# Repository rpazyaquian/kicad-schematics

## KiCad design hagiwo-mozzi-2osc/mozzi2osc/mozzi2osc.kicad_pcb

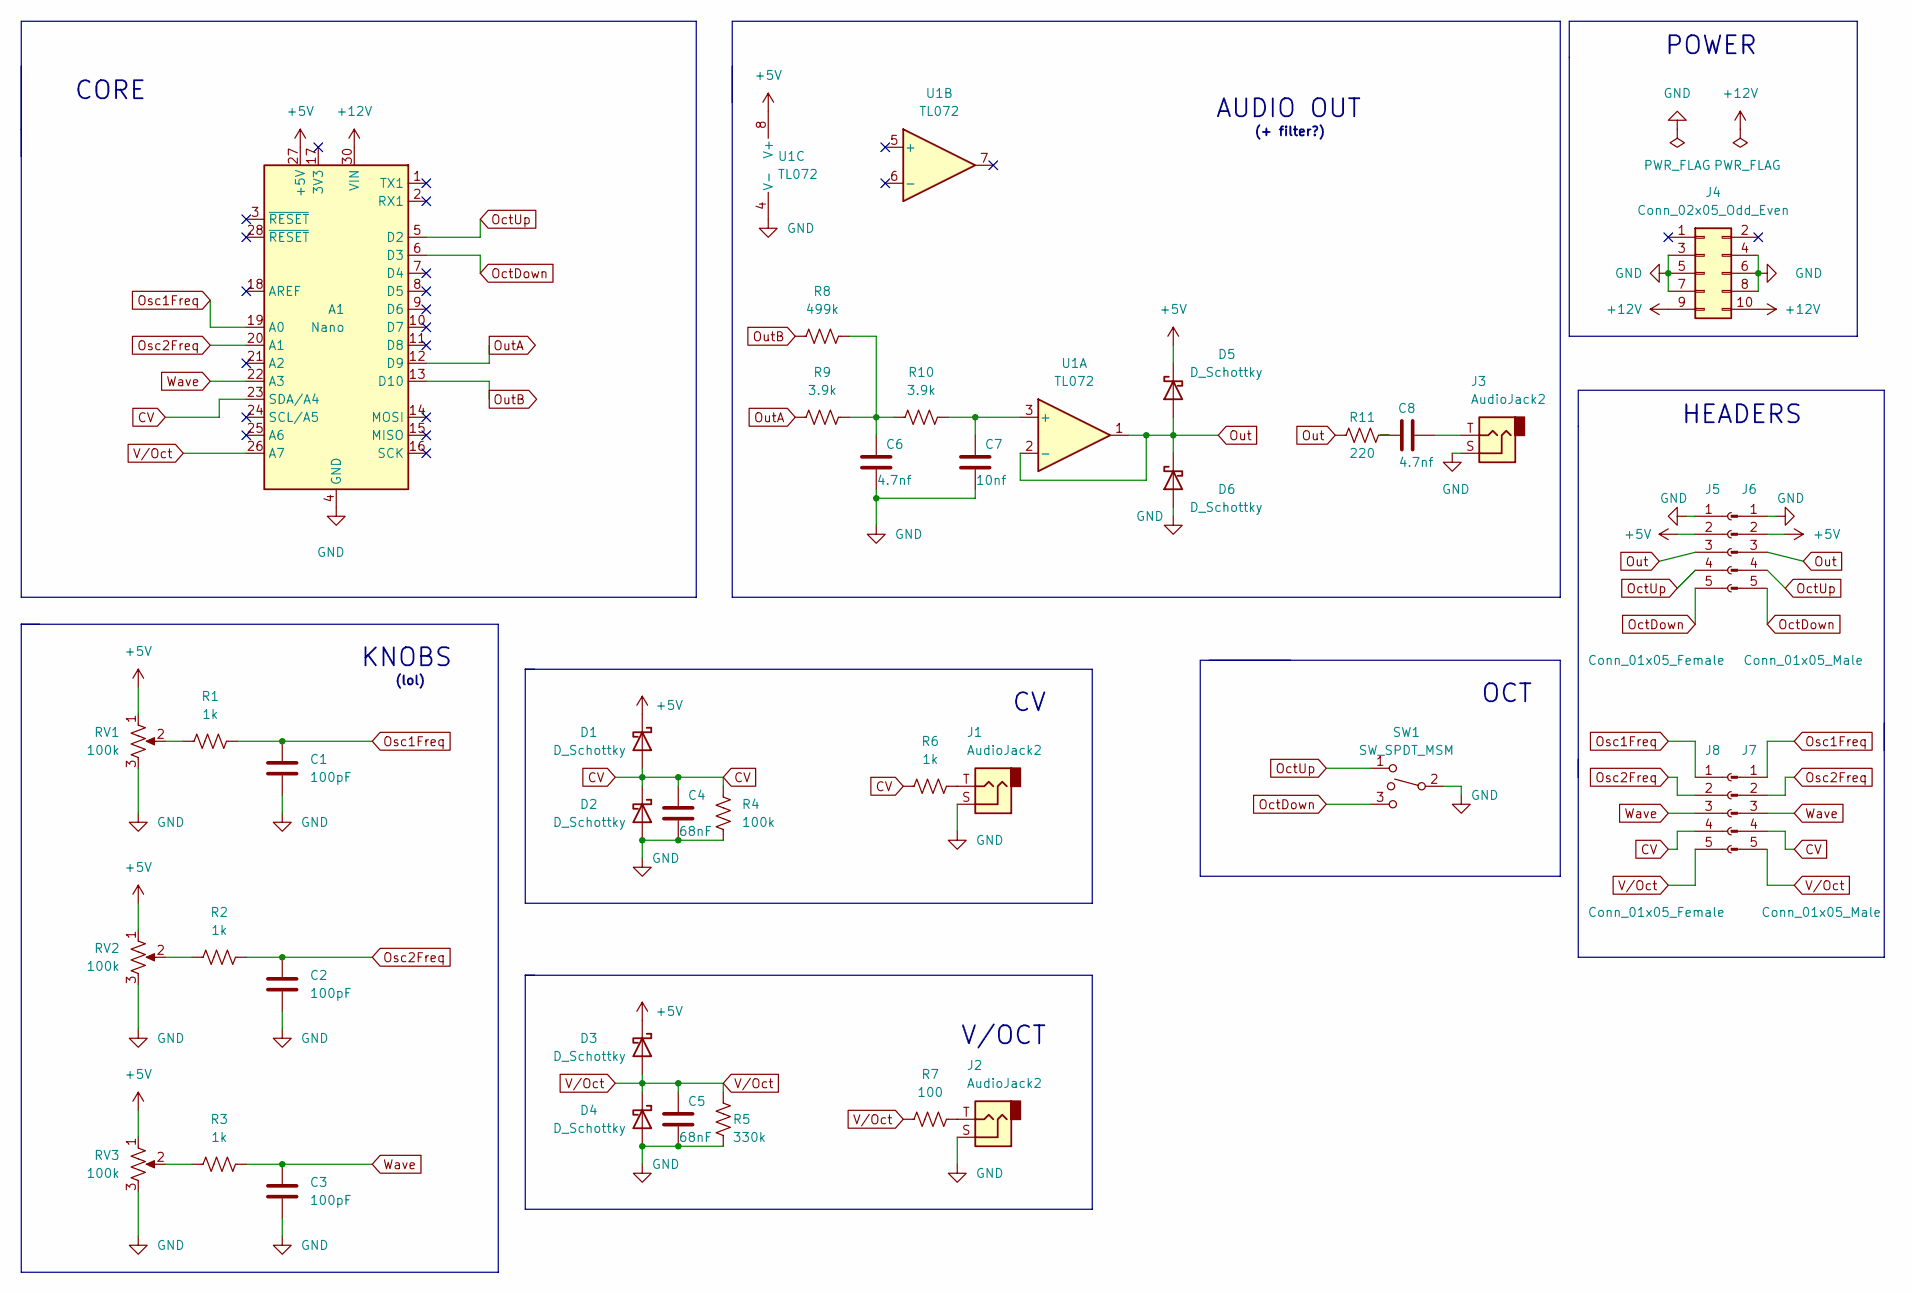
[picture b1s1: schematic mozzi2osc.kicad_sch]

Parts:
A1: Nano; Arduino_Nano
C1, C2, C3: 100pF; C_Disc_D6.0mm_W2.5mm_P5.00mm
C4, C5: 68nF; C_Disc_D6.0mm_W2.5mm_P5.00mm
C6, C8: 4.7nf; C_Disc_D6.0mm_W2.5mm_P5.00mm
C7: 10nf; C_Disc_D6.0mm_W2.5mm_P5.00mm
D1, D2, D3, D4, D5, D6: D_Schottky; D_DO-41_SOD81_P12.70mm_Horizontal
J1, J2, J3: AudioJack2; Jack_3.5mm_QingPu_WQP-PJ398SM_Vertical_CircularHoles
J4: Conn_02x05_Odd_Even; PinHeader_2x05_P2.54mm_Vertical
J5, J8: Conn_01x05_Female; PinSocket_1x05_P2.54mm_Vertical
J6, J7: Conn_01x05_Male; PinHeader_1x05_P2.54mm_Vertical
R1, R2, R3, R6: 1k; R_Axial_DIN0207_L6.3mm_D2.5mm_P10.16mm_Horizontal
R4: 100k; R_Axial_DIN0207_L6.3mm_D2.5mm_P10.16mm_Horizontal
R5: 330k; R_Axial_DIN0207_L6.3mm_D2.5mm_P10.16mm_Horizontal
R7: 100; R_Axial_DIN0207_L6.3mm_D2.5mm_P10.16mm_Horizontal
R8: 499k; R_Axial_DIN0207_L6.3mm_D2.5mm_P10.16mm_Horizontal
R9, R10: 3.9k; R_Axial_DIN0207_L6.3mm_D2.5mm_P10.16mm_Horizontal
R11: 220; R_Axial_DIN0207_L6.3mm_D2.5mm_P10.16mm_Horizontal
RV1, RV2, RV3: 100k; Potentiometer_Alpha_RD901F-40-00D_Single_Vertical
SW1: SW_SPDT_MSM; SW_NKK_D22012P
U1: TL072; DIP-8_W7.62mm_Socket_LongPads

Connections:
+5V: A1.27 (+5V), D1.1 (K), D3.1 (K), D5.1 (K), J5.2, J6.2, RV1.1, RV2.1, RV3.1, U1.8 (V+)
+12V: A1.30 (VIN), J4.9, J4.10
CV: A1.23 (SDA/A4), C4.1, D1.2 (A), D2.1 (K), J7.4, J8.4, R4.1, R6.1
GND: A1.4 (GND), A1.29 (GND), C1.2, C2.2, C3.2, C4.2, C5.2, C6.2, C7.2, D2.2 (A), D4.2 (A), D6.2 (A), J1.S, J2.S, J3.S, J4.3, J4.4, J4.5, J4.6, J4.7, J4.8, J5.1, J6.1, R4.2, R5.2, RV1.3, RV2.3, RV3.3, SW1.2, U1.4 (V-)
unnamed: C6.1, R8.2, R9.2, R10.1
unnamed: C7.1, R10.2, U1.3 (+)
unnamed: C8.1, R11.2
unnamed: C8.2, J3.T
unnamed: J1.T, R6.2
unnamed: J2.T, R7.2
unnamed: R1.1, RV1.2
unnamed: R2.1, RV2.2
unnamed: R3.1, RV3.2
OctDown: A1.6 (D3), J5.5, J6.5, SW1.3
OctUp: A1.5 (D2), J5.4, J6.4, SW1.1
Osc1Freq: A1.19 (A0), C1.1, J7.1, J8.1, R1.2
Osc2Freq: A1.20 (A1), C2.1, J7.2, J8.2, R2.2
Out: D5.2 (A), D6.1 (K), J5.3, J6.3, R11.1, U1.1, U1.2 (-)
OutA: A1.12 (D9), R9.1
OutB: A1.13 (D10), R8.1
V/Oct: A1.26 (A7), C5.1, D3.2 (A), D4.1 (K), J7.5, J8.5, R5.1, R7.1
Wave: A1.22 (A3), C3.1, J7.3, J8.3, R3.2

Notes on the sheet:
KNOBS
HEADERS
AUDIO OUT
(lol)
OCT
V/OCT
POWER
(+ filter?)
CORE

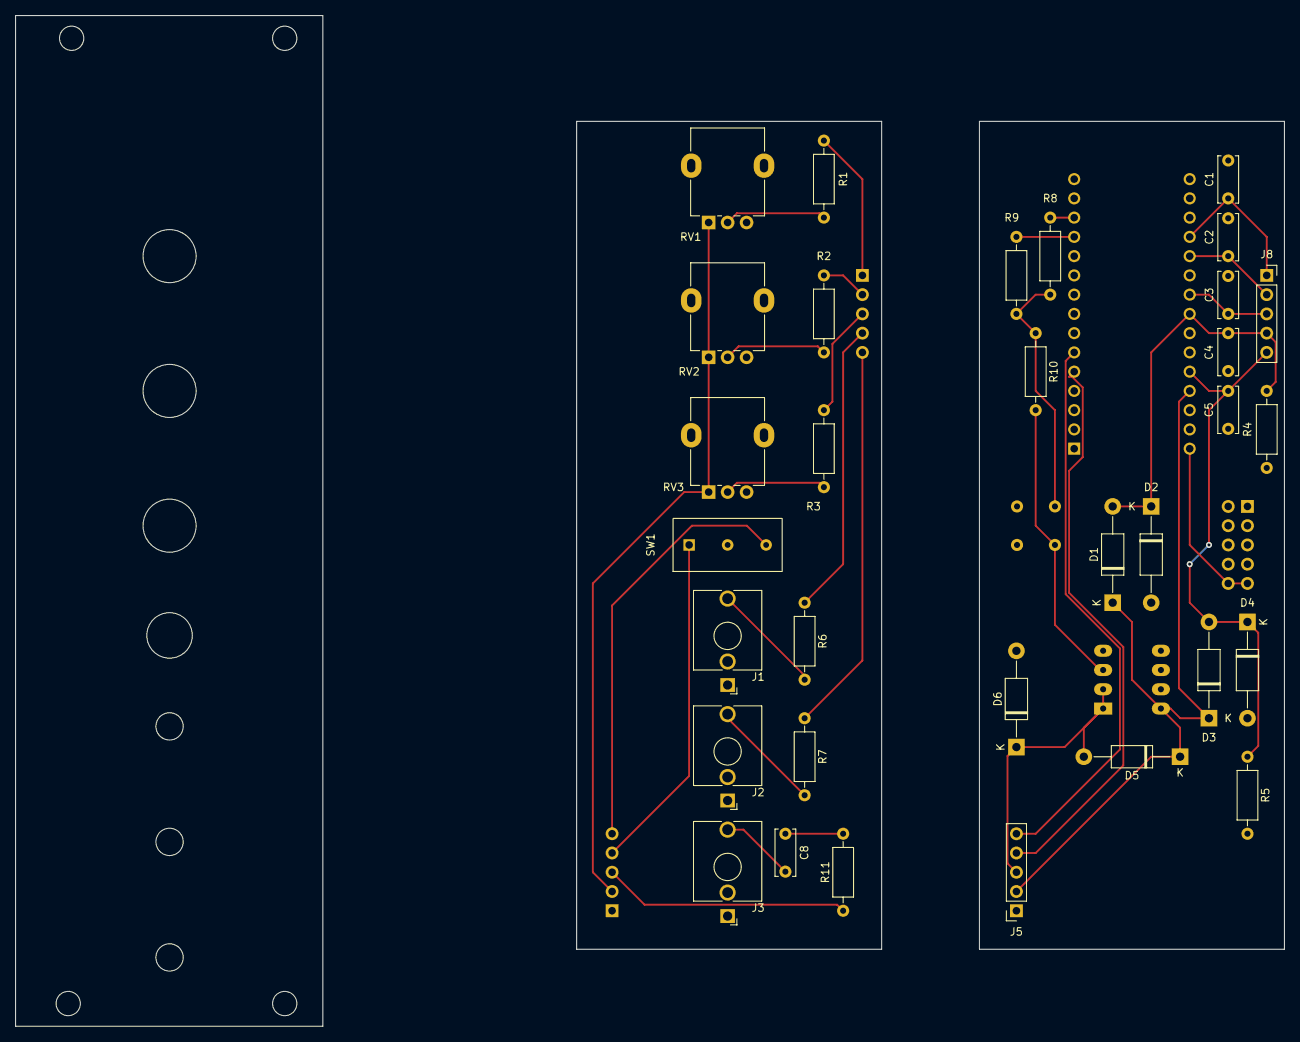
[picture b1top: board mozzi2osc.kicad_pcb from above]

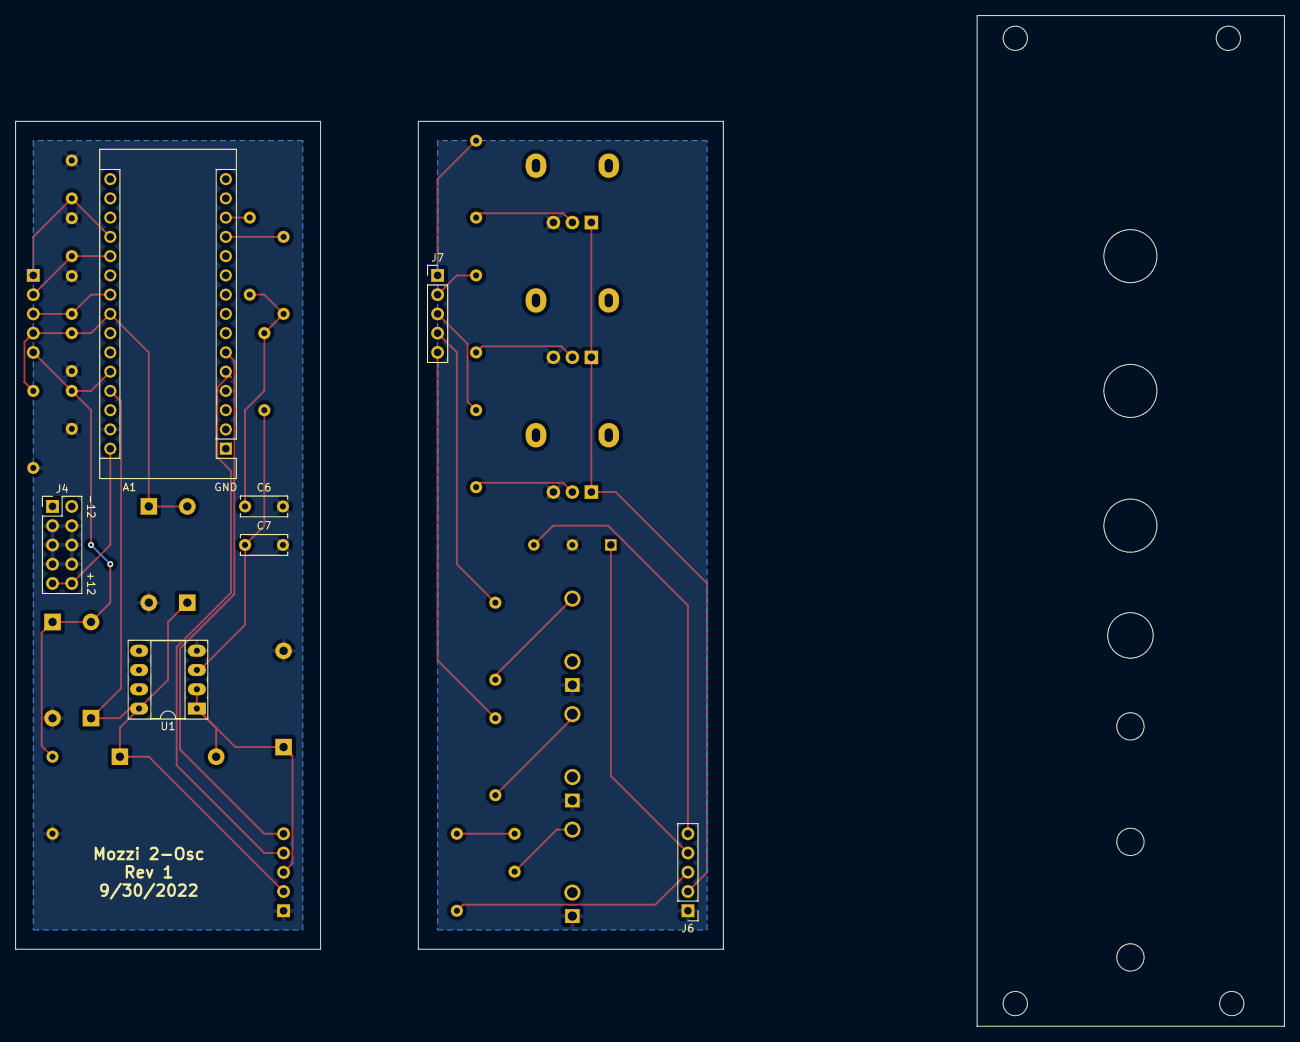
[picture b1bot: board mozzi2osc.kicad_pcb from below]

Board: 2 copper layers, 167.4 x 133.3 mm, 39 parts (7 on the bottom side), 22 nets.

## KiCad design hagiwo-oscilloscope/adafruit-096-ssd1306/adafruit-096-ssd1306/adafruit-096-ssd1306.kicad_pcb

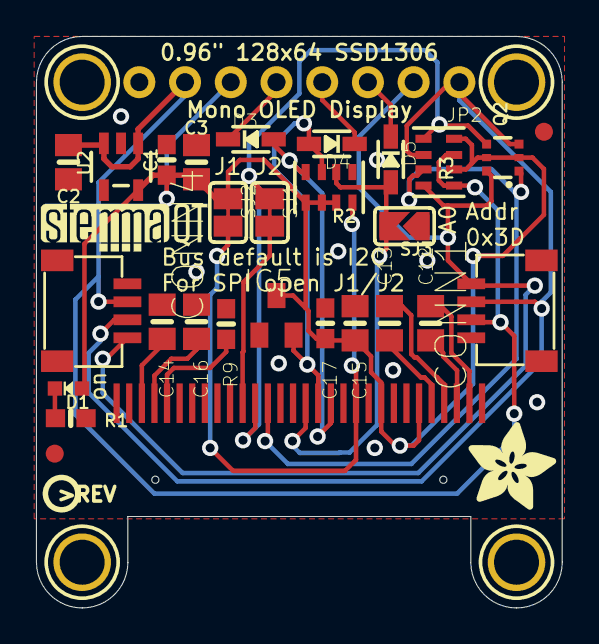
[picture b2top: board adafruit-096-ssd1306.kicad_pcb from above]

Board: 2 copper layers, 29.2 x 31.8 mm, 36 parts (1 on the bottom side), 23 nets.

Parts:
C1, C17: 0.1uF; 0603-NO
C2, C3, C14, C15, C16: 10uF; 0805-NO
C12, C13: 2.2uF; 0805-NO
CONN1, CONN4: STEMMA_I2C_QT; JST_SH4
D1: GREEN; CHIPLED_0603_NOOUTLINE
D3, D4, D5: 1N4148; SOD-323
FID3, FID4: FIDUCIAL_1MM
IC5: APX803; SOT23
JP2: 1X08_ROUND_70
Q2: BSS138; SOT363
R1: 10K; 0603-NO
R2, R3: 10K; RESPACK_4X0603
R9: 390K; 0603-NO
SJ1, SJ2: SOLDERJUMPER_CLOSEDWIRE
SJ3: SOLDERJUMPER_ARROW_NOPASTE
U1: UG-2864HSWEG01; UG-2864HSWEG01_0.96IN_WRAPAROUND
U2: AP2112K-3.3; SOT23-5
U$1, U$17, U$19, U$21: MOUNTINGHOLE2.5; MOUNTINGHOLE_2.5_PLATED
U$8: ADAFRUIT_5MM
U$25: PCBFEAT-REV-040
U$31: STEMMAQT

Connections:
3.3V: C1.1, C3.1, C15.2, C17.2, D1.A, IC5.3, JP2.6, Q2.2, Q2.5, R2.5, R2.6, R2.7, R3.2, R3.4, SJ2.1, U1.6, U1.9, U2.5
CS_3.3V: D3.A, R2.4, U1.13
CS_5.0V: D3.C, JP2.5
D0/SCLK/SCK_3.3V: Q2.1, R3.7, U1.18
D1/MOSI/SDA1_3.3V: Q2.4, R3.5, SJ1.1, U1.19
DC/SA0_3.3V: D5.A, R2.2, SJ3.2, U1.15
DC/SA0_5.0V: D5.C, JP2.3
GND: C1.2, C2.2, C3.2, C14.1, C15.1, C16.1, C17.1, CONN1.1, CONN4.1, IC5.1, JP2.8, R1.2, R2.1, R9.1, SJ3.1, U1.1, U1.8, U1.10, U1.12, U1.29, U1.30, U2.2
unnamed: D1.C, R1.1
unnamed: R2.8, SJ2.2, U1.11
unnamed: R9.2, U1.26
unnamed: C12.2, U1.2
unnamed: C12.1, U1.3
unnamed: C13.2, U1.4
unnamed: C13.1, U1.5
unnamed: C14.2, U1.28
unnamed: C16.2, U1.27
unnamed: SJ1.2, U1.20
RST_3.3V: D4.A, IC5.2, R2.3, U1.14
RST_5.0V: D4.C, JP2.4
SCL: CONN1.4, CONN4.4, JP2.2, Q2.6, R3.8
SDA: CONN1.3, CONN4.3, JP2.1, Q2.3, R3.6
VCC: C2.1, CONN1.2, CONN4.2, JP2.7, R3.1, R3.3, U2.1, U2.3

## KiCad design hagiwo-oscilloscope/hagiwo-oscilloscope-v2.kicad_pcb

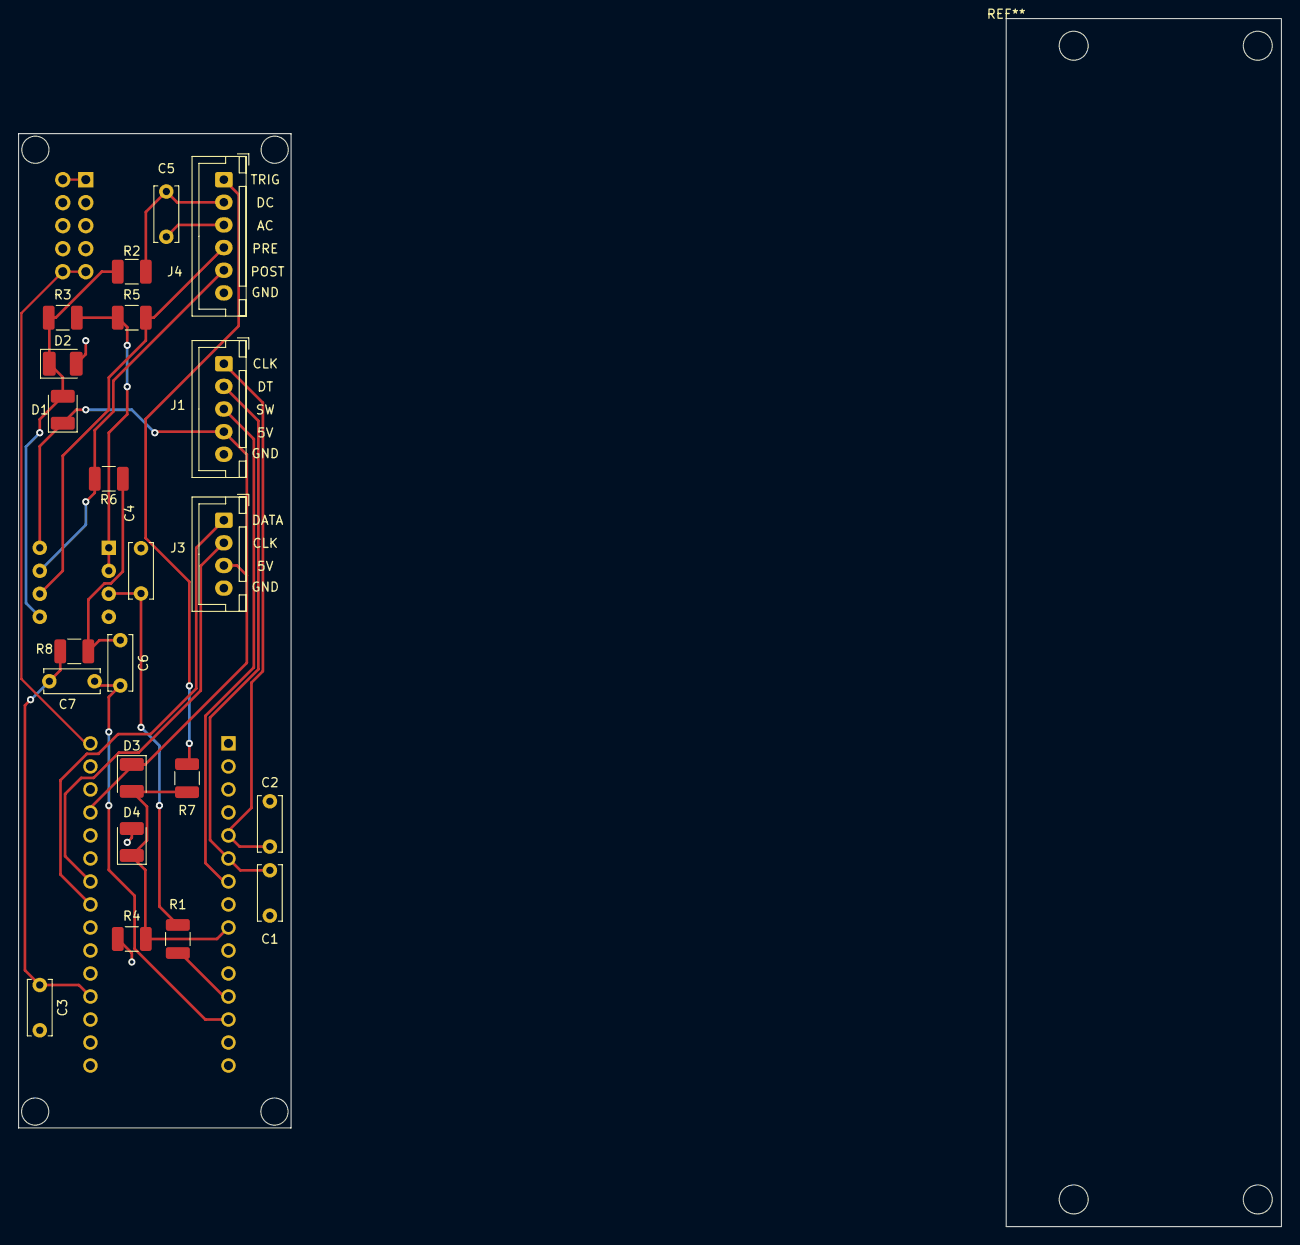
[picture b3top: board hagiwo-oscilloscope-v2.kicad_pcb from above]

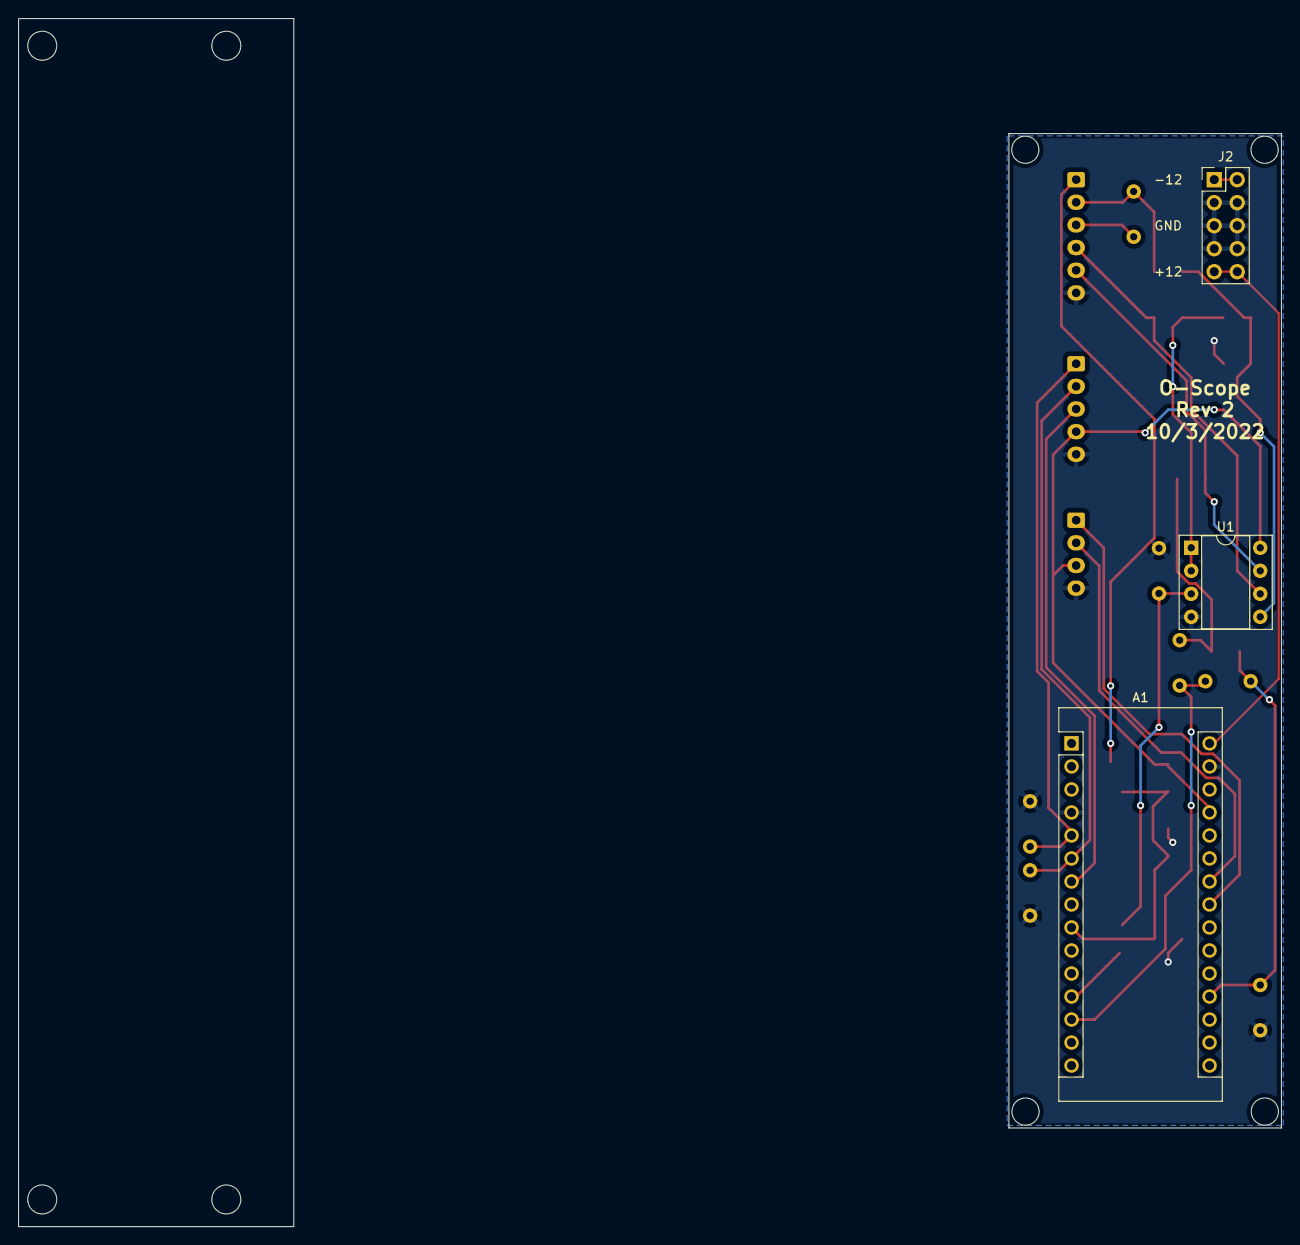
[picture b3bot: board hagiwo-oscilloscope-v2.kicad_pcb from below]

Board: 2 copper layers, 30.1 x 109.8 mm, 25 parts (3 on the bottom side), 22 nets.

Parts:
A1: Nano; Arduino_Nano
C1, C2: 0.01uF; C_Disc_D6.0mm_W2.5mm_P5.00mm
C3: 470pf; C_Disc_D6.0mm_W2.5mm_P5.00mm
C4: 1uF; C_Disc_D6.0mm_W2.5mm_P5.00mm
C5: 4.7 uF; C_Disc_D6.0mm_W2.5mm_P5.00mm
C6, C7: 22 nF; C_Disc_D6.0mm_W2.5mm_P5.00mm
D1, D2, D3, D4: D_Schottky; D_1210_3225Metric_Pad1.42x2.65mm_HandSolder
J1: Encoder Header; JST_XH_B5B-XH-A_1x05_P2.50mm_Vertical
J2: 10-Pin uZeus Power; PinHeader_2x05_P2.54mm_Vertical
J3: OLED Header; JST_XH_B4B-XH-A_1x04_P2.50mm_Vertical
J4: Input Header; JST_XH_B6B-XH-A_1x06_P2.50mm_Vertical
R1, R3: 47k O; R_1210_3225Metric_Pad1.30x2.65mm_HandSolder
R2, R5: 10k O; R_1210_3225Metric_Pad1.30x2.65mm_HandSolder
R4: 100k O; R_1210_3225Metric_Pad1.30x2.65mm_HandSolder
R6, R7, R8: 1k O; R_1210_3225Metric_Pad1.30x2.65mm_HandSolder
U1: Opamp_Dual; DIP-8_W7.62mm_Socket

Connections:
+5V: A1.27 (+5V), D1.1 (K), D3.1 (K), J1.4, J3.3, U1.8 (V+)
+12V: A1.30 (VIN), J2.9, J2.10
-12V: J2.1, J2.2
ACInput: C5.2, J4.3
DCInput: C5.1, J4.2, R2.2
EncoderCLK: A1.5 (D2), C2.1, J1.1
EncoderDT: A1.6 (D3), C1.1, J1.2
EncoderSW: A1.7 (D4), J1.3
ExternalTrigger: A1.9 (D6), D3.2 (A), D4.1 (K), R4.1, R7.2
GND: A1.4 (GND), A1.29 (GND), C1.2, C2.2, C3.2, C4.2, D2.2 (A), D4.2 (A), J1.5, J2.3, J2.4, J2.5, J2.6, J2.7, J2.8, J3.4, J4.6, R4.2, U1.4 (V-)
LowPassInput: A1.13 (D10), C6.1, C7.1
unnamed: C4.1, R1.1, U1.3 (+)
unnamed: C6.2, R6.1, R8.2
unnamed: D1.2 (A), D2.1 (K), R2.1, R3.1, U1.5 (+)
OLEDClock: A1.24 (A5), J3.2
OLEDData: A1.23 (A4), J3.1
OffsetOut: A1.12 (D9), R1.2
OffsetVoltage: R3.2, R5.2, U1.1, U1.2 (-)
PostGain: J4.5, R6.2, U1.7
PreGain: J4.4, R5.1, U1.6 (-)
SignalIn: A1.19 (A0), C3.1, C7.2, R8.1
TriggerJack: J4.1, R7.1

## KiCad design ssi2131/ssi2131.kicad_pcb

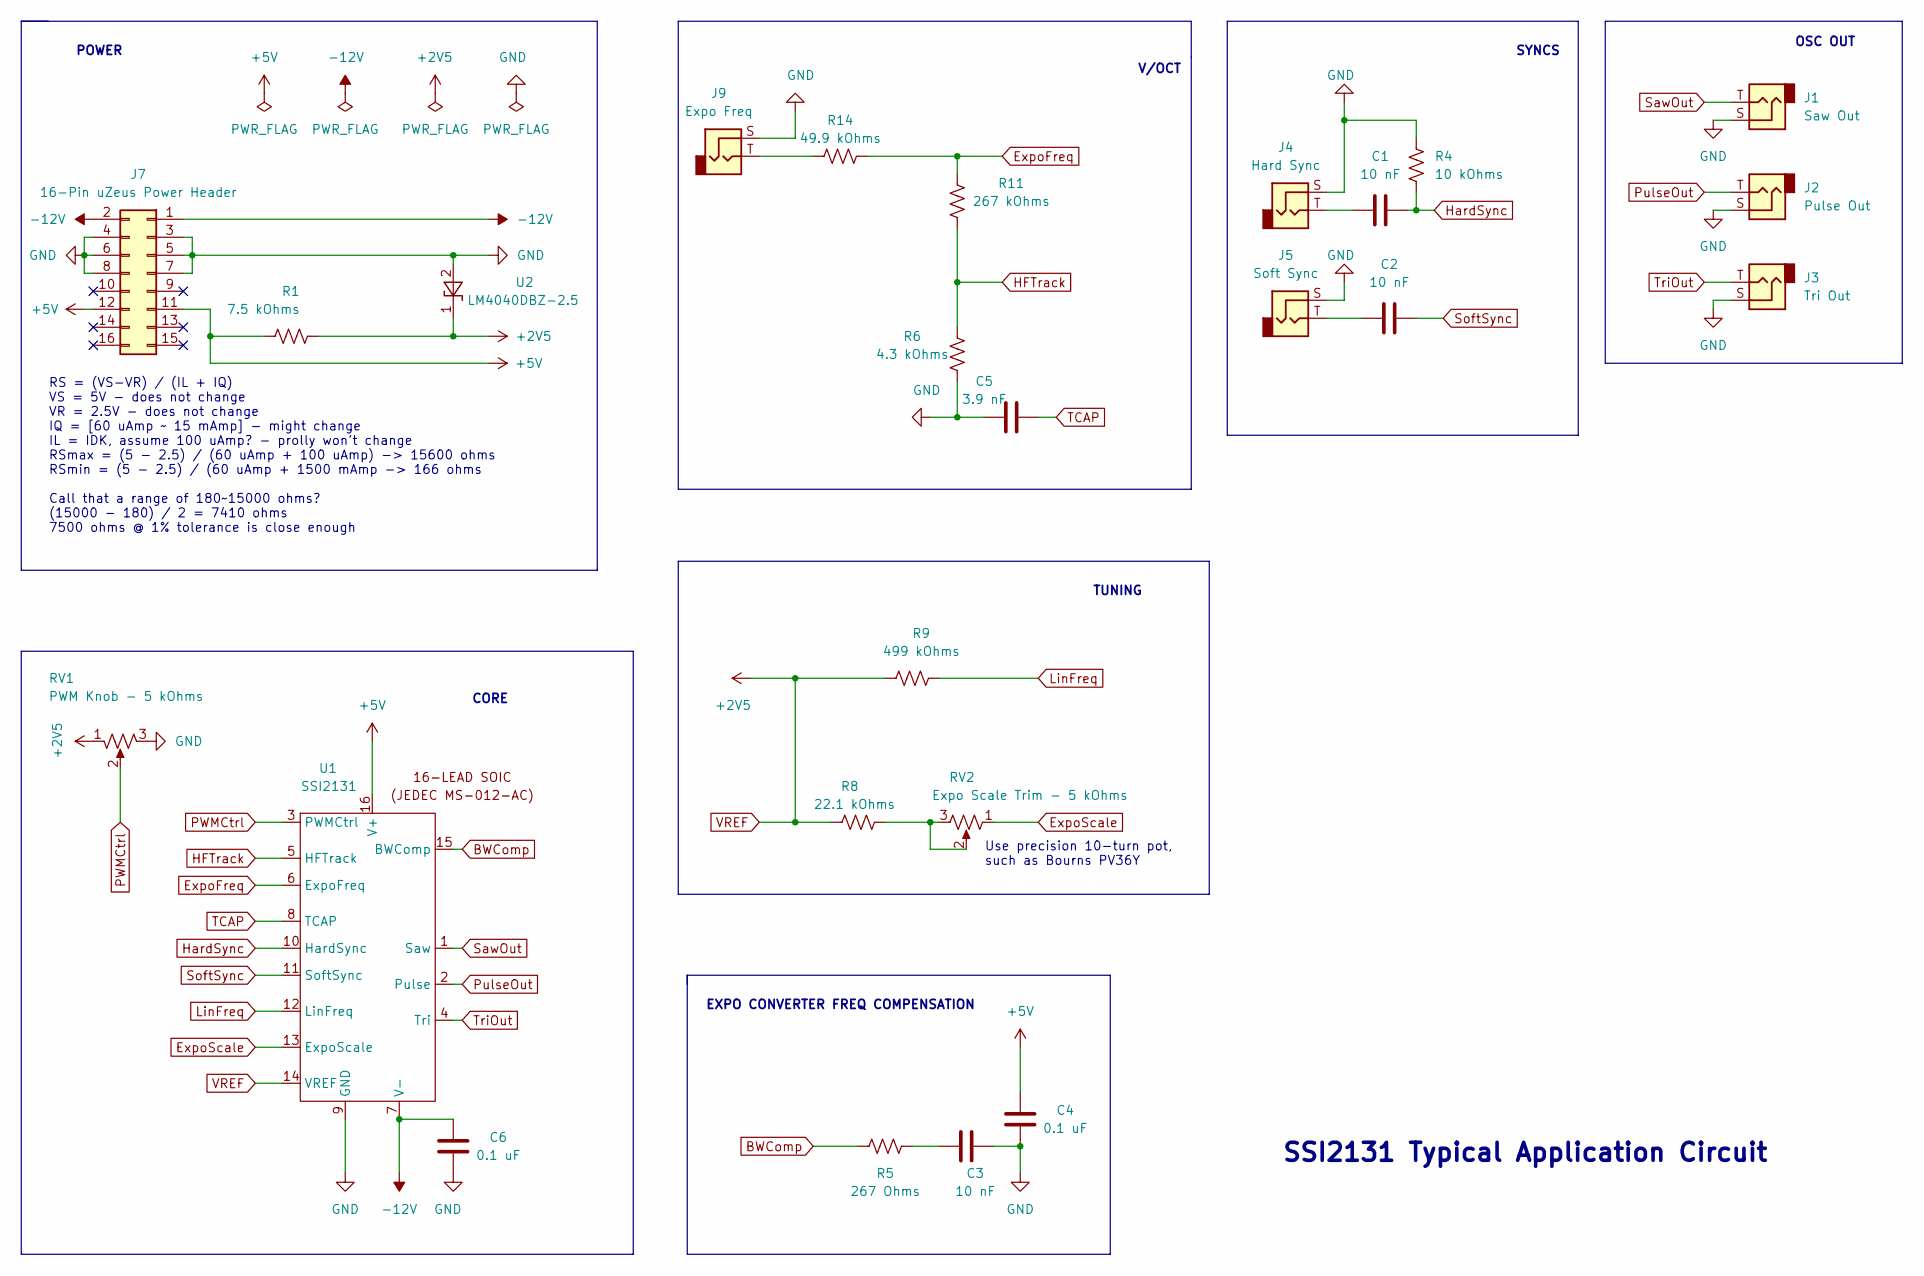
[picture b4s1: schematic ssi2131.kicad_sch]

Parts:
C1, C2, C3: 10 nF; C_Disc_D6.0mm_W2.5mm_P5.00mm
C4, C6: 0.1 uF; C_Disc_D6.0mm_W2.5mm_P5.00mm
C5: 3.9 nF; C_Disc_D6.0mm_W2.5mm_P5.00mm
J1: Saw Out; Jack_3.5mm_QingPu_WQP-PJ398SM_Vertical_CircularHoles
J2: Pulse Out; Jack_3.5mm_QingPu_WQP-PJ398SM_Vertical_CircularHoles
J3: Tri Out; Jack_3.5mm_QingPu_WQP-PJ398SM_Vertical_CircularHoles
J4: Hard Sync; Jack_3.5mm_QingPu_WQP-PJ398SM_Vertical_CircularHoles
J5: Soft Sync; Jack_3.5mm_QingPu_WQP-PJ398SM_Vertical_CircularHoles
J7: 16-Pin uZeus Power Header; PinHeader_2x08_P2.54mm_Vertical
J9: Expo Freq; Jack_3.5mm_QingPu_WQP-PJ398SM_Vertical_CircularHoles
R1: 7.5 kOhms; R_Axial_DIN0207_L6.3mm_D2.5mm_P2.54mm_Vertical
R4: 10 kOhms; R_Axial_DIN0207_L6.3mm_D2.5mm_P2.54mm_Vertical
R5: 267 Ohms; R_Axial_DIN0207_L6.3mm_D2.5mm_P2.54mm_Vertical
R6: 4.3 kOhms; R_Axial_DIN0207_L6.3mm_D2.5mm_P2.54mm_Vertical
R8: 22.1 kOhms; R_Axial_DIN0207_L6.3mm_D2.5mm_P2.54mm_Vertical
R9: 499 kOhms; R_Axial_DIN0207_L6.3mm_D2.5mm_P2.54mm_Vertical
R11: 267 kOhms; R_Axial_DIN0207_L6.3mm_D2.5mm_P2.54mm_Vertical
R14: 49.9 kOhms; R_Axial_DIN0207_L6.3mm_D2.5mm_P2.54mm_Vertical
RV1: PWM Knob - 5 kOhms; Potentiometer_Alpha_RD901F-40-00D_Single_Vertical
RV2: Expo Scale Trim - 5 kOhms; Potentiometer_Bourns_3296W_Vertical
U1: SSI2131; SOIC-16_3.9x9.9mm_P1.27mm
U2: LM4040DBZ-2.5; SOT-23

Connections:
+5V: C4.2, J7.11, J7.12, R1.1, U1.16 (V+)
-12V: C6.2, J7.1, J7.2, U1.7 (V-)
BWComp: R5.1, U1.15 (BWComp)
ExpoFreq: R11.2, R14.2, U1.6 (ExpoFreq)
ExpoScale: RV2.1, U1.13 (ExpoScale)
GND: C3.1, C4.1, C5.2, C6.1, J1.S, J2.S, J3.S, J4.S, J5.S, J7.3, J7.4, J7.5, J7.6, J7.7, J7.8, J9.S, R4.1, R6.2, RV1.3, U1.9 (GND), U2.2 (A)
HFTrack: R6.1, R11.1, U1.5 (HFTrack)
HardSync: C1.2, R4.2, U1.10 (HardSync)
LinFreq: R9.2, U1.12 (LinFreq)
unnamed: C1.1, J4.T
unnamed: C2.2, J5.T
unnamed: J9.T, R14.1
unnamed: C3.2, R5.2
unnamed: R8.1, RV2.2, RV2.3
PWMCtrl: RV1.2, U1.3 (PWMCtrl)
PulseOut: J2.T, U1.2 (Pulse)
SawOut: J1.T, U1.1 (Saw)
SoftSync: C2.1, U1.11 (SoftSync)
TCAP: C5.1, U1.8 (TCAP)
TriOut: J3.T, U1.4 (Tri)
VREF: R1.2, R8.2, R9.1, RV1.1, U1.14 (VREF), U2.1 (K)

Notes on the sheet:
SSI2131 Typical Application Circuit
Use precision 10-turn pot, such as Bourns PV36Y
RS = (VS-VR) / (IL + IQ) VS = 5V - does not change VR = 2.5V - does not change IQ = [60 uAmp ~ 15 mAmp] - might change IL = IDK, assume 100 uAmp? - prolly won't change RSmax = (5 - 2.5) / (60 uAmp + 100 uAmp) -> 15600 ohms RSmin = (5 - 2.5) / (60 uAmp + 1500 mAmp -> 166 ohms Call that a range of 18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
OSC OUT
POWER
CORE
SYNCS
TUNING
EXPO CONVERTER FREQ COMPENSATION
V/OCT

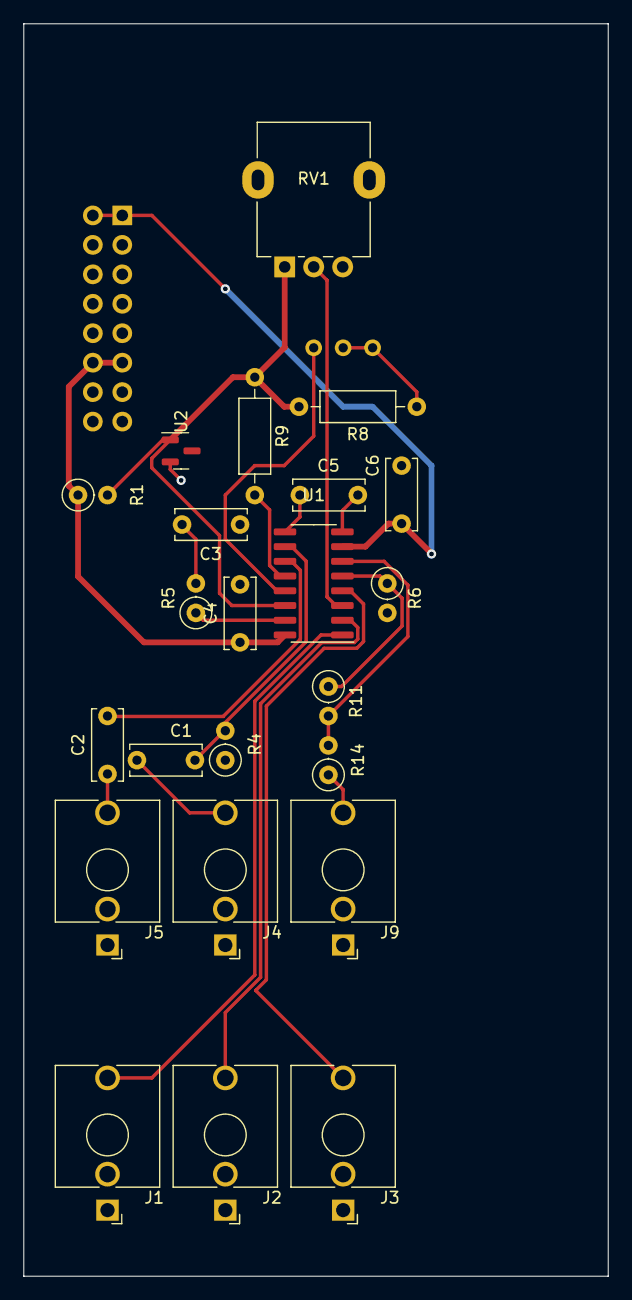
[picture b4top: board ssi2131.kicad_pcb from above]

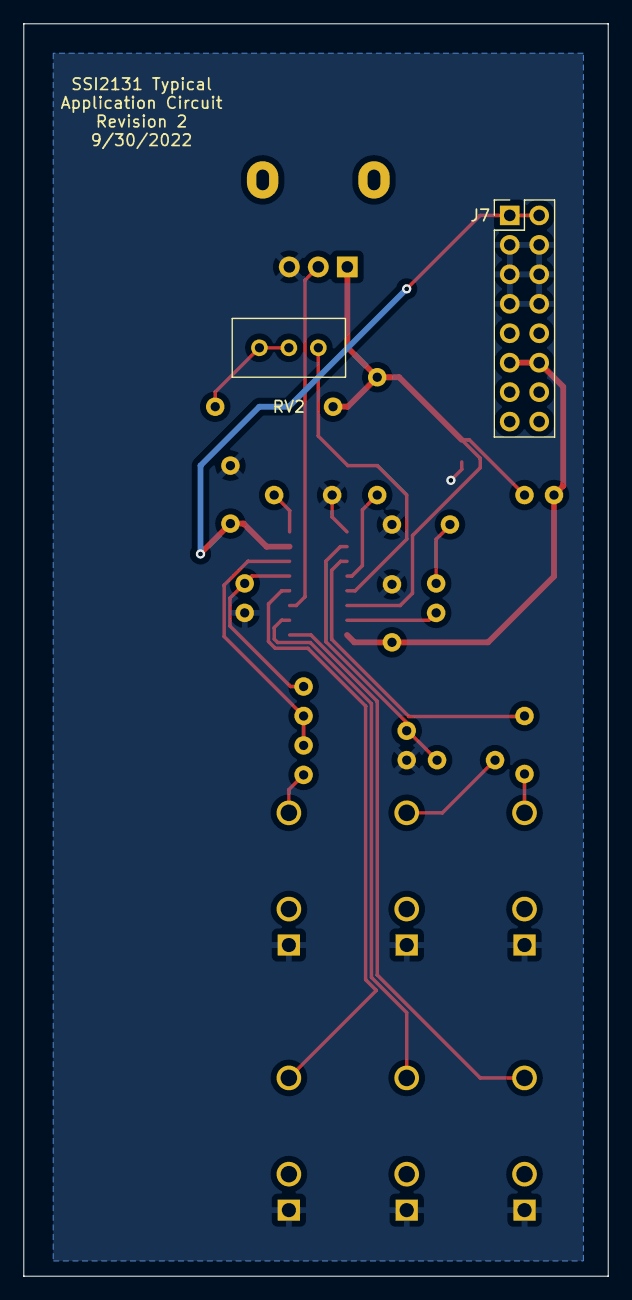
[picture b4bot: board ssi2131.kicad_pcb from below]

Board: 2 copper layers, 50.4 x 108.0 mm, 25 parts (2 on the bottom side), 21 nets.

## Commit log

2022-09-27 add notes on regulator current and resistor
2022-09-28 starting on pcb
2022-09-28 update fp-info-cache, whatever that is
2022-09-30 PCB attempt 1
2022-09-30 Add revision info, adjust tracks and spacing
2022-09-30 rework PCB layout
2022-09-30 rework PCB layout, but more
2022-10-02 mozzi 2osc updates; oscilloscope
2022-10-03 further work on oscilloscope
2022-10-03 o-scope rev2
2022-10-04 defining panel pcb
2022-10-05 general fuckery
2022-10-05 i dont know what im doing
2022-10-06 panelize 2osc
2022-10-06 add switch 3d model
2022-10-06 add 3d model for audio jacks
2022-10-13 add openscad blank panel SVGs
2022-10-13 blank 4hp pdf; some other projects to work on
2022-10-19 sequential switch setup
2022-10-19 general stuff; start hagiwo cv-midi converter
